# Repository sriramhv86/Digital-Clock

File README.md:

# Digital-Clock
Contains code for both new and old projects.
Check out the instructable for more info.
http://www.instructables.com/id/Digital-Wall-clock

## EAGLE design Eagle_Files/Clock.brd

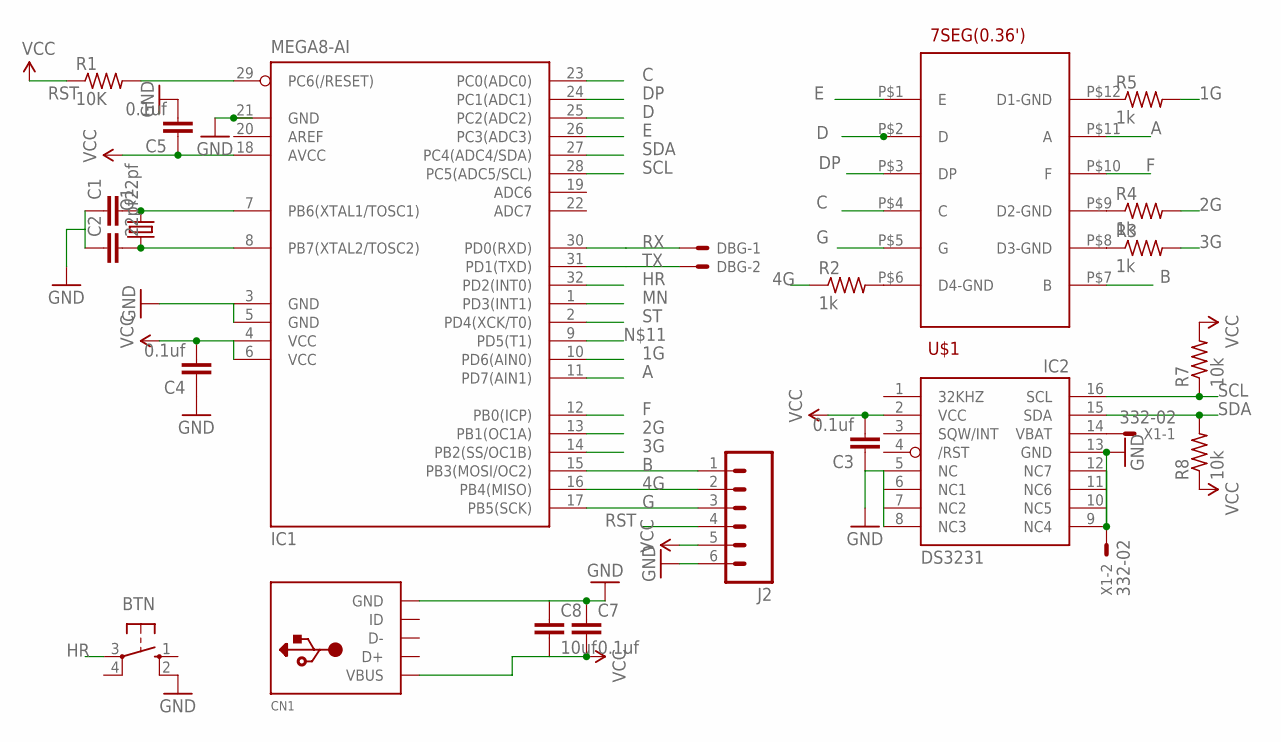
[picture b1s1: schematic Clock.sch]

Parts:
BTN: 10-XX; B3F-10XX
C1, C2: 22pf; C0603
C3, C4, C5, C7: 0.1uf; C0603
C8: 10uf; C0603
CN1: USBMINIB; USB-MINIB
DBG: 332-02
IC1: MEGA8-AI; TQFP32-08
IC2: DS3231/SO; SO16W
J2: M06LOCK_LONGPADS; 1X06_LOCK_LONGPADS
Q1: CRYSTALHC49S; HC49/S
R1: 10K; R0603
R2, R3, R4, R5: 1k; R0603
R7, R8: 10k; R0603
U$1: 7SEG7SEG12; DIP127SEG.36'
X1: 332-02

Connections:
1G: IC1.10 (PD6(AIN0)), R5.2
2G: IC1.13 (PB1(OC1A)), R4.2
3G: IC1.14 (PB2(SS/OC1B)), R3.2
4G: IC1.16 (PB4(MISO)), J2.2, R2.1
A: IC1.11 (PD7(AIN1)), U$1.P$11 (A)
B: IC1.15 (PB3(MOSI/OC2)), J2.1, U$1.P$7 (B)
C: IC1.23 (PC0(ADC0)), U$1.P$4 (C)
D: IC1.25 (PC2(ADC2)), U$1.P$2 (D)
DP: IC1.24 (PC1(ADC1)), U$1.P$3 (DP)
E: IC1.26 (PC3(ADC3)), U$1.P$1 (E)
F: IC1.12 (PB0(ICP)), U$1.P$10 (F)
G: IC1.17 (PB5(SCK)), J2.3, U$1.P$5 (G)
GND: BTN.2 (S1), C1.1, C2.1, C3.1, C4.1, C5.2, C7.1, C8.1, CN1.GND, IC1.3 (GND), IC1.5 (GND), IC1.21 (GND), IC2.5 (NC), IC2.6 (NC1), IC2.7 (NC2), IC2.8 (NC3), IC2.9 (NC4), IC2.10 (NC5), IC2.11 (NC6), IC2.12 (NC7), IC2.13 (GND), J2.6, X1.2
HR: BTN.3, IC1.32 (PD2(INT0))
MN: IC1.1 (PD3(INT1))
unnamed: IC2.14 (VBAT), X1.1
unnamed: R3.1, U$1.P$8 (D3-GND)
unnamed: R4.1, U$1.P$9 (D2-GND)
unnamed: R5.1, U$1.P$12 (D1-GND)
unnamed: C1.2, IC1.7 (PB6(XTAL1/TOSC1)), Q1.2
unnamed: R2.2, U$1.P$6 (D4-GND)
unnamed: C2.2, IC1.8 (PB7(XTAL2/TOSC2)), Q1.1
RST: IC1.29 (PC6(/RESET)), J2.4, R1.2
RX: DBG.1, IC1.30 (PD0(RXD))
SCL: IC1.28 (PC5(ADC5/SCL)), IC2.16 (SCL), R7.1
SDA: IC1.27 (PC4(ADC4/SDA)), IC2.15 (SDA), R8.2
ST: IC1.2 (PD4(XCK/T0))
TX: DBG.2, IC1.31 (PD1(TXD))
VCC: C3.2, C4.2, C5.1, C7.2, C8.2, CN1.VBUS, IC1.4 (VCC), IC1.6 (VCC), IC1.18 (AVCC), IC2.2 (VCC), J2.5, R1.1, R7.2, R8.1

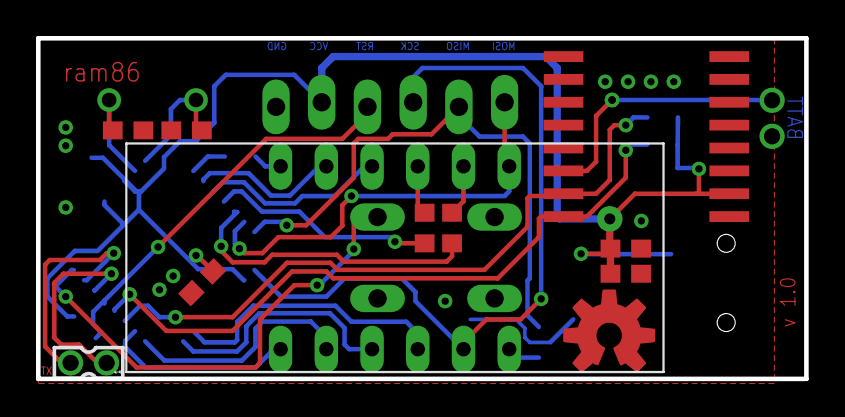
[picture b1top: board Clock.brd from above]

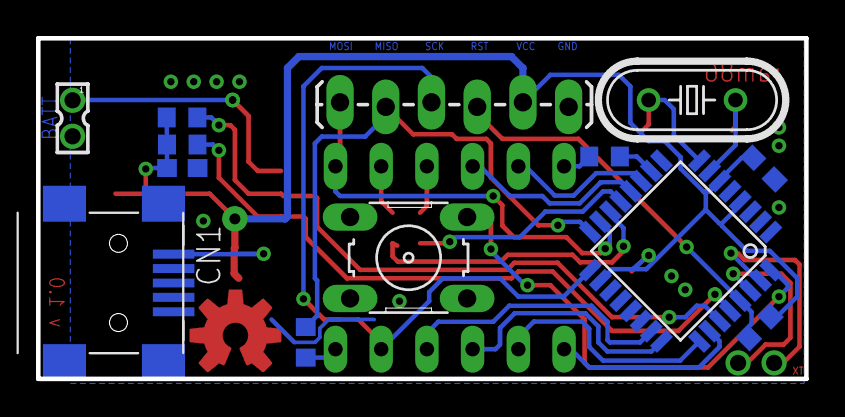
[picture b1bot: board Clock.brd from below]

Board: 2 copper layers, 42.7 x 18.9 mm, 24 parts (13 on the bottom side), 27 nets.

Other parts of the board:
LOGO2: OSHW-LOGOM-COPPER; OSHW-LOGO-M_COPPER

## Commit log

2017-04-20 Adding first version of the board
2017-04-20 Adding all the codes (both for new and old version)
2017-07-16 Adding usb connector intead of DC jack

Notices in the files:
parts and their libraries:
SparkFun-Aesthetics: Licensing: Creative Commons ShareAlike 4.0 International - https://creativecommons.org/licenses/by-sa/4.0
